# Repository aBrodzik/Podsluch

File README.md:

Jak uruchomić aplikacje?

cd podsluch
python manage.py runserver

Najlepiej otworzyć w firefoxie: http://127.0.0.1:8000/wiretapp/

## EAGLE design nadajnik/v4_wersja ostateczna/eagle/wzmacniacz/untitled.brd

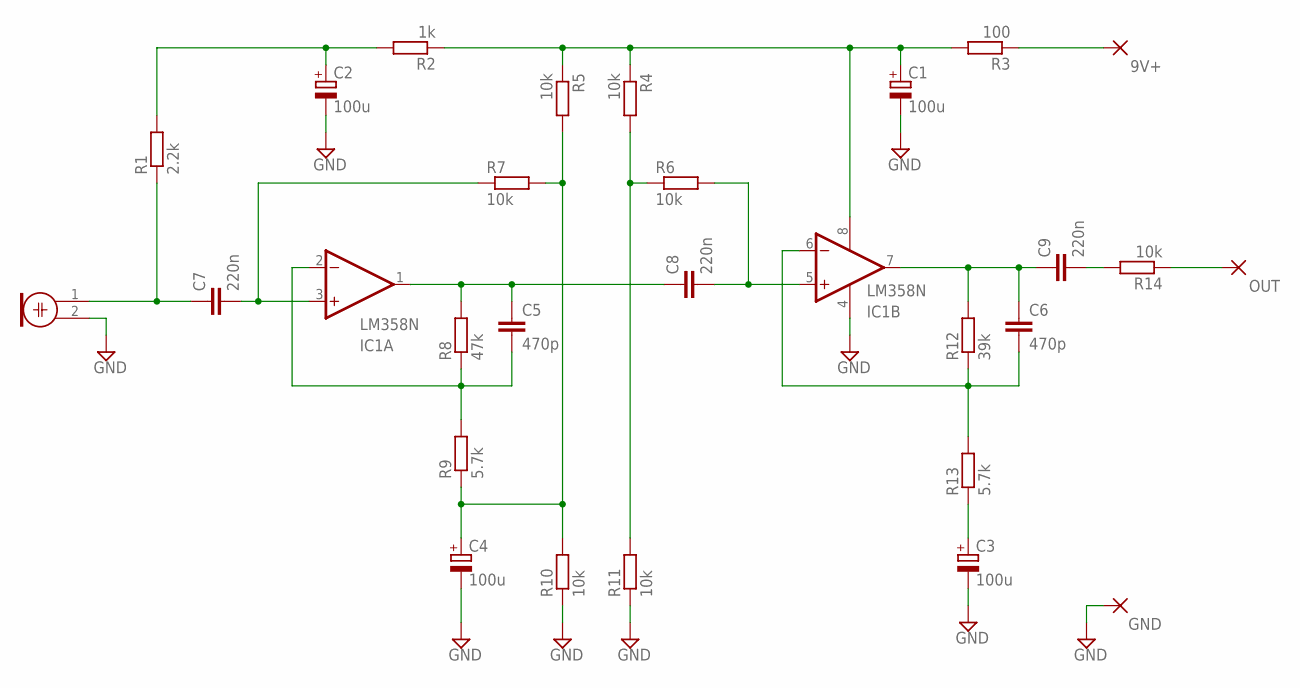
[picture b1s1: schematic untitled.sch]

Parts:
9V+: 3,81/1,4
C1, C2, C3, C4: 100u; E2-5
C5, C6: 470p; C025-025X050
C7, C8, C9: 220n; C050-025X075
GND: 3,81/1,4
IC1: LM358N; DIL08
M1: ELECTRET_MICROPHON-F6050AP; F6050AP
OUT: 3,81/1,4
R1: 2.2k; 0207/10
R2: 1k; 0207/10
R3: 100; 0207/10
R4, R5, R6, R7, R10, R11, R14: 10k; 0207/10
R8: 47k; 0207/10
R9, R13: 5.7k; 0207/10
R12: 39k; 0207/10

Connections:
GND: C1.-, C2.-, C3.-, C4.-, GND.1, IC1.4 (V-), M1.2, R10.1, R11.1
unnamed: C7.2, IC1.3 (+IN), R7.1
unnamed: C5.1, C8.1, IC1.1 (OUT), R8.2
unnamed: C5.2, IC1.2 (-IN), R8.1, R9.2
unnamed: C4.+, R5.2, R7.2, R9.1, R10.2
unnamed: C8.2, IC1.5 (+IN), R6.2
unnamed: R4.2, R6.1, R11.2
unnamed: C7.1, M1.1, R1.1
unnamed: C2.+, R1.2, R2.2
unnamed: C1.+, IC1.8 (V+), R2.1, R3.2, R4.1, R5.1
unnamed: 9V+.1, R3.1
unnamed: C6.2, IC1.6 (-IN), R12.1, R13.2
unnamed: C3.+, R13.1
unnamed: C6.1, C9.1, IC1.7 (OUT), R12.2
unnamed: OUT.1, R14.1
unnamed: C9.2, R14.2

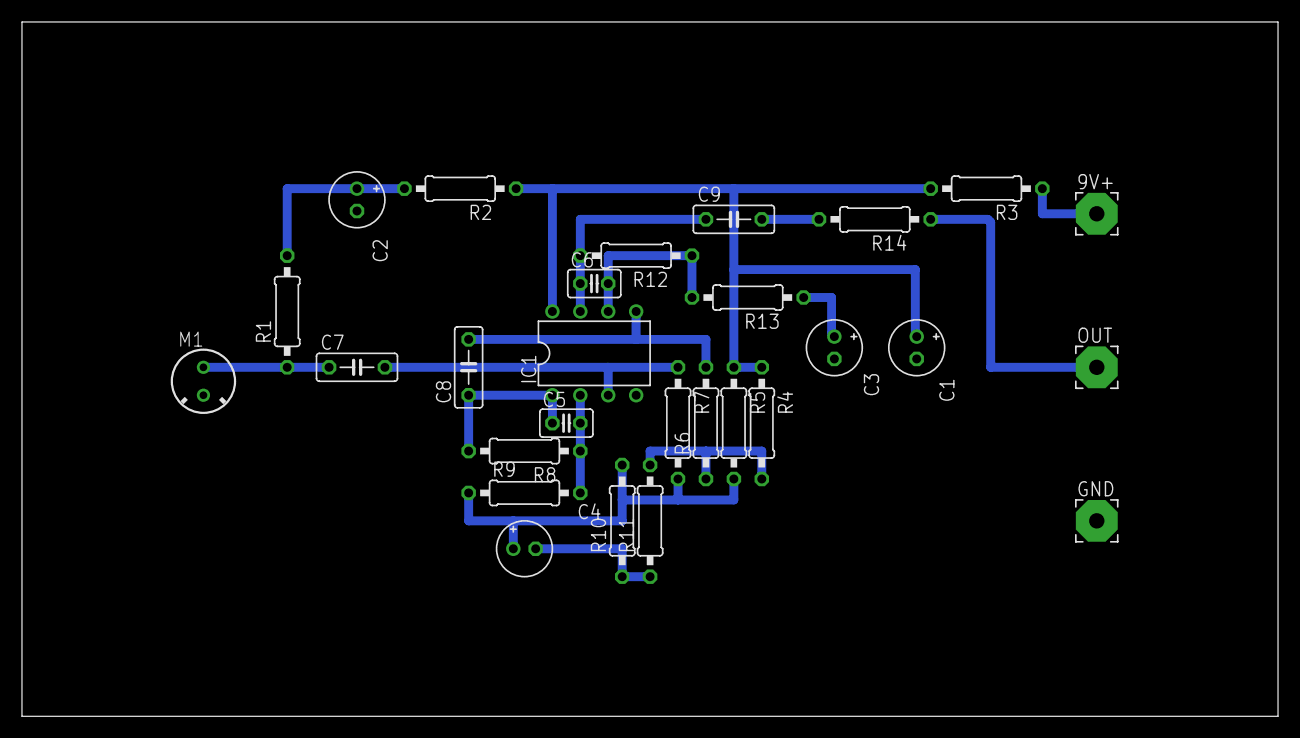
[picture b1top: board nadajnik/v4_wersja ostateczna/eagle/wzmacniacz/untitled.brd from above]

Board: 2 copper layers, 114.3 x 63.2 mm, 28 parts (0 on the bottom side), 16 nets.

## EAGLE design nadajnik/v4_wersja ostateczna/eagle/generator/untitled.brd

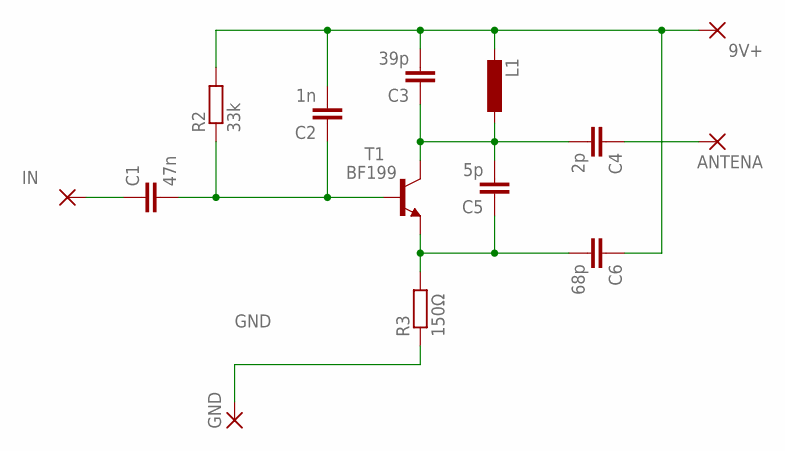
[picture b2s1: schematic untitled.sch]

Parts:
9V+: 3,81/1,4
ANTENA: 3,81/1,4
C1: 47n; C025-025X050
C2: 1n; C025-025X050
C3: 39p; C025-025X050
C4: 2p; C025-025X050
C5: 5p; C025-025X050
C6: 68p; C025-025X050
GND: 3,81/1,4
IN: 3,81/1,4
L1: L-EU0207/7; 0207/7
R2: 33k; 0207/10
R3: 150Ω; 0207/10
T1: BF199; TO92

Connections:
GND: GND.1, R3.1
unnamed: C1.1, IN.1
unnamed: C1.2, C2.1, R2.1, T1.1 (B)
unnamed: C5.1, C6.2, R3.2, T1.2 (E)
unnamed: C3.1, C4.2, C5.2, L1.1, T1.3 (C)
unnamed: 9V+.1, C2.2, C3.2, C6.1, L1.2, R2.2
unnamed: ANTENA.1, C4.1

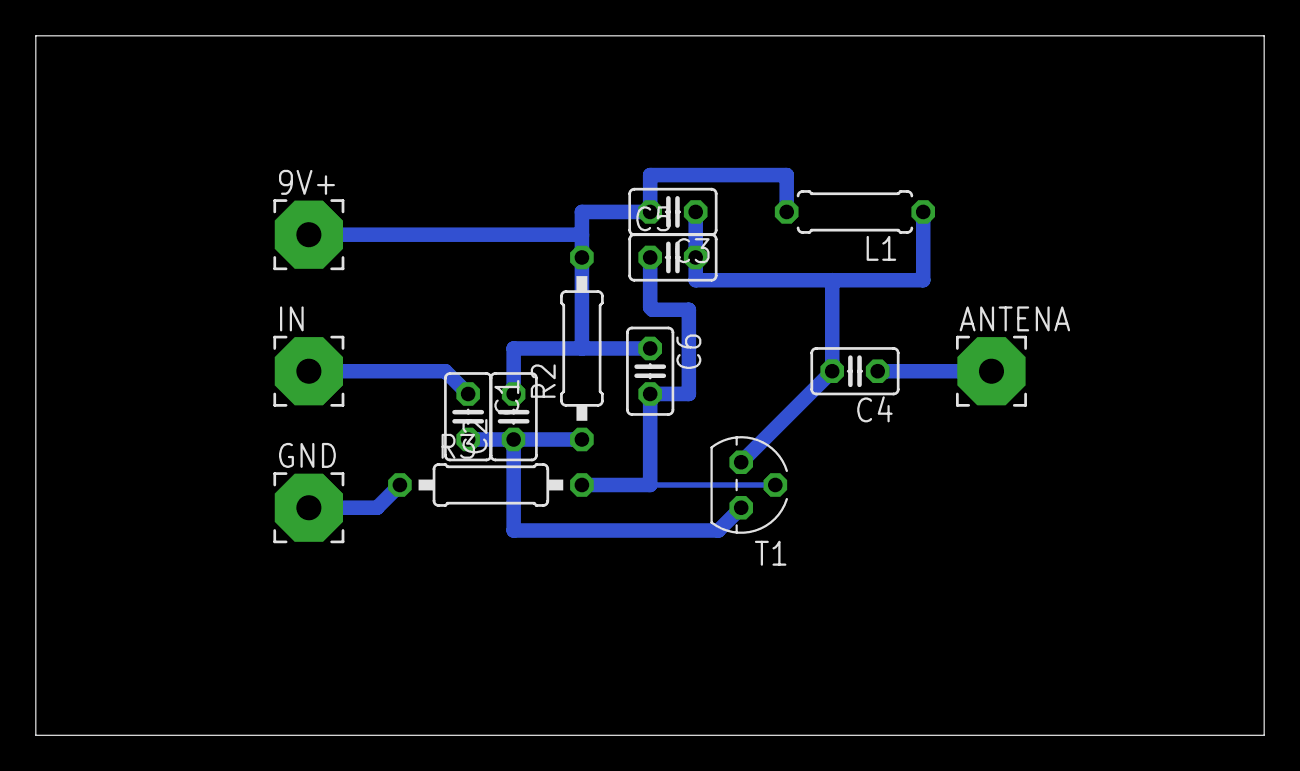
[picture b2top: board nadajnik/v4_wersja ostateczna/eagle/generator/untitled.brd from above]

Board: 2 copper layers, 68.6 x 39.0 mm, 14 parts (0 on the bottom side), 7 nets.

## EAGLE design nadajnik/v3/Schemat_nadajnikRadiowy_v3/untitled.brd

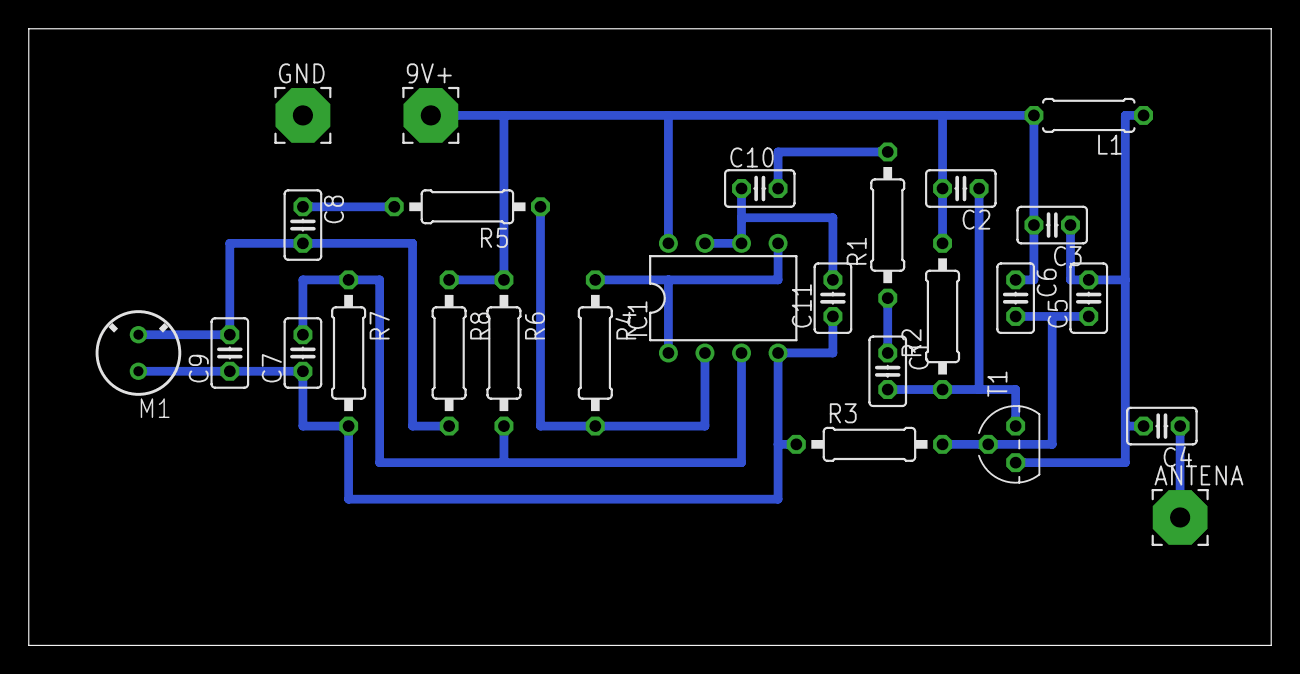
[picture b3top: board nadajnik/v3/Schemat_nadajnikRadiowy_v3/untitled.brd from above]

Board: 2 copper layers, 86.3 x 42.9 mm, 26 parts (0 on the bottom side), 14 nets.

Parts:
9V+: 3,81/1,4
ANTENA: 3,81/1,4
C1: 47n; C025-025X050
C2, C7, C9, C11: 1n; C025-025X050
C3: 39p; C025-025X050
C4: 2p; C025-025X050
C5: 5p; C025-025X050
C6: 68p; C025-025X050
C8: 10u; C025-025X050
C10: 22u; C025-025X050
GND: 3,81/1,4
IC1: LM358N; DIL08
L1: 0207/7
M1: ELECTRET_MICROPHON-F6050AP; F6050AP
R1: 220; 0207/10
R2: 33k; 0207/10
R3: 150Ω; 0207/10
R4: 150k; 0207/10
R5: 300; 0207/10
R6: 4.7k; 0207/10
R7: 4.7; 0207/10
R8: 1.8k; 0207/10
T1: BF199; TO92

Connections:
GND: C7.1, C9.1, C11.1, GND.1, IC1.4, M1.1, R3.1, R7.2
unnamed: C10.2, R1.2
unnamed: C1.1, R1.1
unnamed: C1.2, C2.1, R2.1, T1.1
unnamed: C10.1, C11.2, IC1.6, IC1.7
unnamed: C5.1, C6.2, R3.2, T1.2
unnamed: C3.1, C4.2, C5.2, L1.1, T1.3
unnamed: 9V+.1, C2.2, C3.2, C6.1, IC1.8, L1.2, R2.2, R6.1, R8.1
unnamed: ANTENA.1, C4.1
unnamed: IC1.1, IC1.5, R4.1
unnamed: IC1.2, R4.2, R5.1
unnamed: C7.2, IC1.3, R6.2, R7.1
unnamed: C8.1, R5.2
unnamed: C8.2, C9.2, M1.2, R8.2

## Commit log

2021-02-27 schemat szkieletu/hello world
2021-02-28 helloWorld 1.1
2021-02-28 hotfix
2021-03-01 ta sama aplikacja, ale z innym frameworkiem, frienship ended with flask, now Django is my new friend
2021-06-10 usuniecie zbednych plikow
2021-06-10 akrualizacja nadajnika
2021-06-10 Odtwarzacz plików lokalnych
2021-06-10 flask i ślepy zaułek
2021-06-10 Od teraz pliki wav otwierają się w firefoxie, czasem w chromie
2021-06-10 Add README.md
2021-06-10 wycinanie, usuwanie, wzmacnianie; mp3-ki zmienione nwa wavy
2021-06-10 poprawka
2021-06-10 praca nad trzecia wersja
2021-06-10 sprzątanie
2021-06-10 Upload New File
2021-06-10 model wzmacniacza
2021-06-10 nadajnik
2021-06-10 prototypy live
2021-06-10 foto
2021-06-10 Add new file; zmiana odtwarzania na transmisje
2021-06-10 nadajnik v3 plytka pcb
2021-06-10 zmiana odtwarzania na transmisje
2021-06-10 dodanie funkcji w takim wygladzie jak dziala dotychczas; zakomentowalem bo na innym komputerze nie zadziala bo username jest inny
2021-06-10 dodanie info o vps
2021-06-10 design apki is ready
2021-06-10 design apki is ready #4
2021-06-10 poprawki po merge'u
2021-06-10 design apki is ready #3
2021-06-10 design apki is ready #2
2021-06-11 hotfix 2
2021-06-11 hotfix 3
2021-06-12 streamowanie z wykorzystaniem 206 partial content
2021-06-12 dodanie daty
2021-06-12 dodanie .decode("utf-8") (nie wiem w sumie czy to potrzebny commit ale dodaje dla spójności plików)
2021-06-12 dodanie sciezki serwera icecast
2021-06-12 konfig icecasta
2021-06-12 finalne poprawki
2021-06-13 gui update
2021-06-13 usuniecie strefy czasowej z nazwy pliku nagrania
2021-06-13 zmiana netcata na icecast
2021-06-13 poprawa poprzedniego kommita (zła ścieżka)
2021-06-15 poprawa nadajnika
